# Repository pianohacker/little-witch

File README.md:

# Little WitCH

The Little WitCH is a tiny but capable dev board for the WCH32V307, boasting:

- The WCH32V307 itself, with a single RISC-V RV32IMACF core
- Gigabit Ethernet via the MXL86110C PHY
- Raspberry-Pi-compatible I/O (with caveats), exposing:
  - Two SPI buses
  - Two I2C buses
  - PCM audio out
  - SDIO/eMMC
  - and/or 28 3.3V GPIO pins
- USB-C 2.0
- USB-1.1 via Raspberry-Pi-Zero-compatible test points
- Tag-Connect TC2030 SWD debugging

## Raspberry Pi compatibility

The WCH32V307's pin remapping can't make it a perfect match for the Raspberry Pi's peripherals. The
biggest caveat is the SPI and PCM outputs, which are all multiplexed together and overlapping:

- SPI3 is exposed on the same pins as the Pi's SPI0 bus.
- PCM is exposed on the same pins as the Pi, but only supports output.
- SPI2 can be exposed on the same pins as the Pi's SPI1 bus, _but_ these pins overlap with the MDIO bus
  of the Ethernet PHY. Also, as these pins overlap with the PCM pins, SPI2 must be switched to by
  cutting and resoldering three solder jumpers below the USB-C port.

That said, this should still allow compatibility with a wide number of Pi Zero / Pi 4 HATs. Will
mention specific examples here as they are tested.

## Solder jumper reconfiguration

There are three sets of solder jumpers that can modify the behavior of this board:

- The jumpers mentioned above, which collectively switch pins 12, 35, and 40 between SPI2 and PCM
  (via I2S3). These default to PCM. **Note:** to be explicit, to switch to SPI2 on these pins, the
  bridge between the first two pads of all three jumpers must be cut and the 2nd and 3rd jumpers
  solder-bridged.
- A jumper to set the value of BOOT1. This defaults to 0.
- A jumper to enable the power LED, which defaults to lit.

## Authors

This is a collaboration between Jesse Weaver (pianohacker) and [Pikkolo Assembly](https://www.pikkoloassembly.com/).

## License

Little WitCH © 2026 by Jesse Weaver is licensed under CC BY-NC-SA 4.0. To view a copy of this license, visit https://creativecommons.org/licenses/by-nc-sa/4.0/

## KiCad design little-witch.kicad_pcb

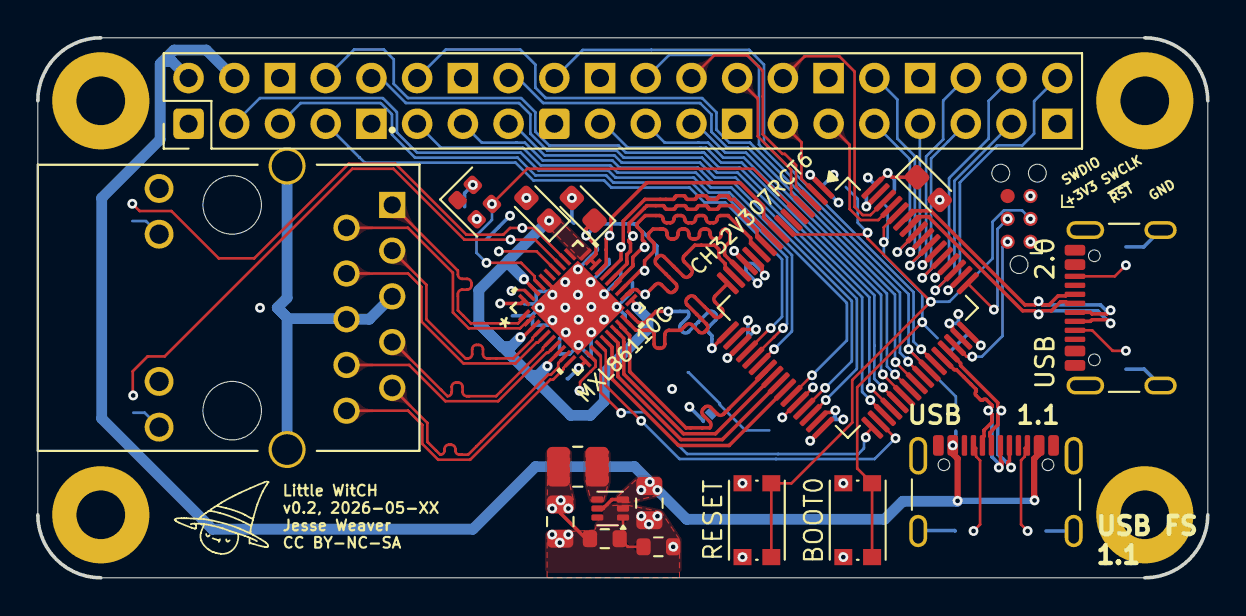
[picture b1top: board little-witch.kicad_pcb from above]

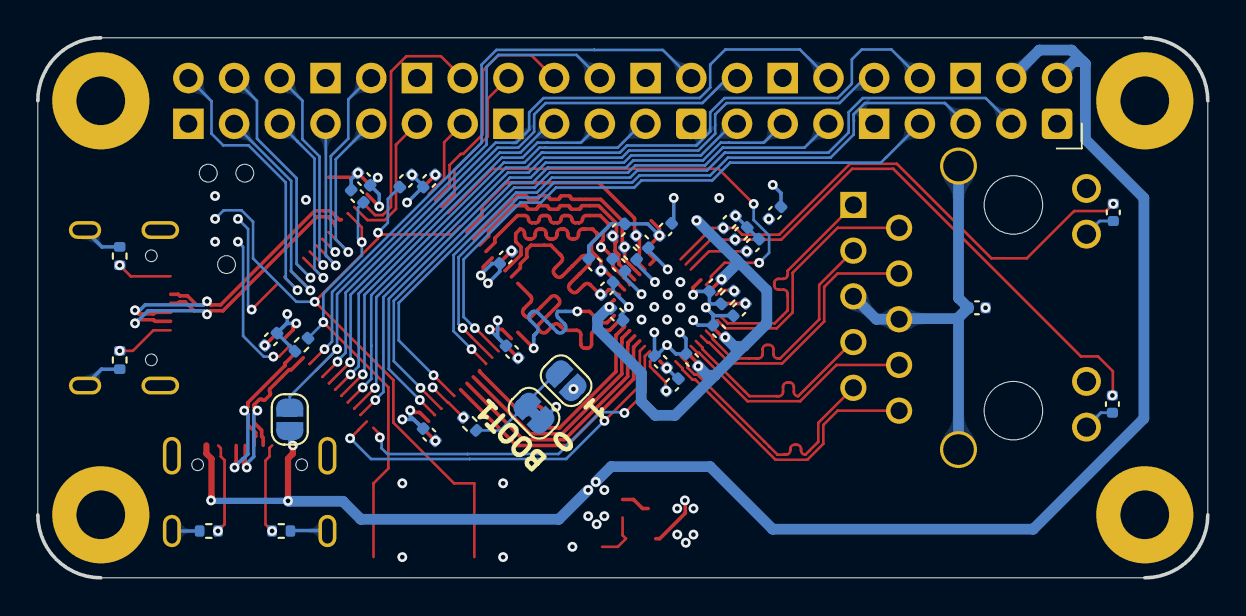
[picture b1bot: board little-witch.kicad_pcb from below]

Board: 4 copper layers, 65.0 x 30.0 mm, 62 parts (40 on the bottom side), 79 nets.

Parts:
C1, C7, C10: 10u; CP_EIA-2012-12_Kemet-R
C2, C3, C4, C5, C6, C8, C9, C11, C14, C18, C19, C20, C22, C23, C24, C26, C27: 100n; C_0402_1005Metric
C12: 4.7u; C_0805_2012Metric
C13: 22u; C_0805_2012Metric
H1, H2, H3, H4: MountingHole_Pad; MountingHole_2.7mm_M2.5_Pad
J1, J4: GCT-USB4105; USB_C_Receptacle_GCT_USB4105-xx-A_16P_TopMnt_Horizontal
J2: TMJG0803HENL; RJ45_TMJG0803HENL
J3: Conn_ARM_SWD_TagConnect_TC2030-NL; Tag-Connect_TC2030-IDC-NL_2x03_P1.27mm_Vertical
J5: Conn_02x20_Odd_Even; PinHeader_2x20_P2.54mm_Vertical
JP3, JP5: SolderJumper_2_Open; SolderJumper-2_P1.3mm_Open_RoundedPad1.0x1.5mm
JP4: SolderJumper_2_Open; SolderJumper-2_P1.3mm_Bridged_RoundedPad1.0x1.5mm
L1: 1u; L_1008_2520Metric
R3, R4, R8, R9: 5.1k; R_0402_1005Metric
R5, R17, R18, R19, R20, R21, R22: 1K; C_0402_1005Metric
R7, R10: 10k; R_0402_1005Metric
R11, R12: 100; C_0402_1005Metric
R13: 2.49K ±1%; R_0402_1005Metric
R14, R15, R16: 4.7K; C_0402_1005Metric
R23: 453K ±1%; R_0603_1608Metric
R24: 100K ±1%; R_0603_1608Metric
SW1: RESET; SW_Push_1P1T_NO_CK_KMR2
SW2: BOOT0; SW_Push_1P1T_NO_CK_KMR2
U1: CH32V307RCT6; LQFP-64_10x10mm_P0.5mm
U2: MXL86110C-AQB-R; QFN40_5X5_MXL
U3: TPS62A0568PDRLR; SOT-563
Y1: SIT8008BI-73-33N-25.000000; Oscillator_SMD_SiT_PQFN-4Pin_2.0x1.6mm

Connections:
+3V3: C1.1, C2.1, C3.1, C4.1, C5.1, C6.1, C9.1, C10.1, C11.1, C13.1, C14.1, C20.1, C22.1, C23.1, J2.11, J2.13, J3.1 (VCC), J5.1, J5.17, JP3.1 (A), L1.2, R5.2, R14.1, R15.1, R16.1, R21.1, R22.1, R23.2, SW2.1, U1.1 (VBAT), U1.13 (VDDA), U1.19 (VDD_4), U1.32 (VIO_1), U1.48 (VDD_2), U1.64 (VIO_3), U2.11 (VDDA3V3), U2.28 (VDDP), U2.29 (VDD3V3), U2.40 (VDDA3V3), Y1.4 (Vdd)
/ETH_CFG_LDO1: R16.2, U2.34 (GPHY_LED2/CFG_LDO1)
/ETH_SHIELD: C27.1, J2.5 (CT), J2.6 (CT__1), J2.SH (SHIELD)
/PA4: J5.7, U1.20 (DAC0/ADC4/PA4)
/PA5: J5.5, U1.21 (DAC1/ADC5/PA5)
/PA6: J5.3, U1.22 (ADC6/PA6)
/PA8: J5.12, U1.41 (PA8)
/PA9: J5.22, JP5.2 (B), U1.42 (PA9)
/PA10: J5.18, U1.43 (PA10)
/PA15: J5.40, U1.50 (PA15)
/PB1: J5.11, U1.27 (ADC9/PB1)
/PB2: R7.2, U1.28 (BOOT1/PB2)
/PB3: J5.33, U1.55 (PB3)
/PB4: J5.32, U1.56 (PB4)
/PB5: J5.31, U1.57 (PB5)
/PB8: J5.29, U1.61 (PB8)
/PB9: J5.28, U1.62 (PB9)
/PB10: J5.13, U1.29 (PB10)
/PB11: J5.15, U1.30 (PB11)
/PB14: J5.10, U1.35 (PB14)
/PB15: J5.8, U1.36 (PB15)
/PC6: J5.19, U1.37 (PC6/RXP)
/PC7: J5.21, U1.38 (PC7/RXN)
/PC8: J5.23, U1.39 (PC8/TXP)
/PC9: J5.16, U1.40 (PC9/TXN)
/PC10: J5.37, U1.51 (PC10)
/PC11: J5.38, U1.52 (PC11)
/PC12: J5.35, U1.53 (PC12)
/PC13: J5.27, U1.2 (PC13/TAMPER-RTC)
/PC14: J5.24, U1.3 (PC14/OSC32_IN)
/PC15: J5.26, U1.4 (PC15/OSC32_OUT)
/PD2: J5.36, U1.54 (PD2)
/TD1+: J2.1 (TD1+), U2.1 (TPIAP)
/TD1-: J2.2 (TD1-), U2.2 (TPIAN)
/TD2+: J2.3 (TD2+), U2.4 (TPIBP)
/TD2-: J2.4 (TD2-), U2.5 (TPIBN)
/TD3+: J2.7 (TD3+), U2.6 (TPICP)
/TD3-: J2.8 (TD3-), U2.7 (TPICN)
/TD4+: J2.9 (TD4+), U2.9 (TPIDP)
/TD4-: J2.10 (TD4-), U2.10 (TPIDN)
ETH_LED1: R11.2, R14.2, U2.32 (GPHY_LED0/CFG_EXT)
ETH_LED2: R12.2, R15.2, U2.33 (GPHY_LED1/CFG_LDO0)
ETH_MDC: U1.33 (PB12), U2.13 (MDC)
ETH_MDIO: U1.34 (PB13), U2.14 (MDIO)
ETH_RESET: R5.1, U2.12 (HRSTN)
ETH_RXC: R20.2, U1.8 (PC0/ADC10), U2.27 (RX_CLK/PHYAD1)
ETH_RXD0: R21.2, U1.10 (PC2/ADC12), U2.25 (RXD0/RXDLY)
ETH_RXD1: R19.2, U1.11 (PC3/ADC13), U2.24 (RXD1/TXDLY)
ETH_RXD2: R22.2, U1.14 (ADC0/WKUP/PA0), U2.23 (RXD2/PLLOFF)
ETH_RXD3: R17.2, U1.15 (ADC1/PA1), U2.22 (RXD3/PHYAD0)
ETH_RX_CTL: R18.2, U1.9 (PC1/ADC11), U2.26 (RX_CTL/PHYAD2)
ETH_TXC: U1.16 (ADC2/PA2), U2.19 (TX_CTL)
ETH_TXD0: U1.23 (ADC7/PA7), U2.18 (TXD0)
ETH_TXD1: U1.24 (PC4/ADC14), U2.17 (TXD1)
ETH_TXD2: U1.25 (PC5/ADC15), U2.16 (TXD2)
ETH_TXD3: U1.26 (ADC8/PB0), U2.15 (TXD3)
ETH_TX_CTL: U1.17 (ADC3/PA3), U2.20 (TX_CLK)
GND: C1.2, C2.2, C3.2, C4.2, C5.2, C6.2, C7.2, C8.1, C9.2, C10.2, C11.2, C12.2, C13.2, C18.2, C19.2, C20.2, C22.2, C23.2, C24.2, C26.2, C27.2, H1.1 (1_1), H2.1 (1_1), H3.1 (1_1), H4.1 (1_1), J1.A1 (GND), J1.A12 (GND), J1.B1 (GND), J1.B12 (GND), J1.SH (SHIELD), J3.5 (GND), J4.A1 (GND), J4.A12 (GND), J4.B1 (GND), J4.B12 (GND), J4.SH (SHIELD), J5.6, J5.9, J5.14, J5.20, J5.25, J5.30, J5.34, J5.39, JP4.1 (A), R3.2, R4.1, R8.2, R9.1, R10.1, R13.2, R17.1, R18.1, R19.1, R20.1, R24.1, SW1.1, U1.12 (VSSA), U1.18 (VSS_4), U1.31 (VSS_1), U1.47 (VSS_2), U1.63 (VSS_3), U2.36 (XTAL1), U2.41 (GND), U3.2 (GND), Y1.2 (GND)
NRST: C8.2, J3.3 (~RESET), SW1.2, U1.7 (NRST)
unnamed: J1.A5 (CC1), R3.1
unnamed: J1.B5 (CC2), R4.2
unnamed: J2.12, R11.1
unnamed: J2.14, R12.1
unnamed: J4.A5 (CC1), R8.1
unnamed: J4.B5 (CC2), R9.2
unnamed: JP3.2 (B), JP4.2 (B), R7.1
unnamed: C14.2, R10.2, SW2.2, U1.60 (BOOT0)
unnamed: R13.1, U2.39 (RCAL)
unnamed: R23.1, R24.2, U3.1 (FB)
unnamed: L1.1, U3.4 (SW)
SWCLK: J3.4 (SWCLK), U1.49 (SWCLK/PA14)
SWDIO: J3.2 (SWDIO), U1.46 (SWDIO/PA13)
SYS_CLK: U1.5 (OSC_IN/PD0), U2.37 (XTAL2/CLK), Y1.3 (OUT)
USB1_DN: J1.A7 (D-), J1.B7 (D-), U1.44 (USB1_DM/PA11)
USB1_DP: J1.A6 (D+), J1.B6 (D+), U1.45 (USB1_DP/PA12)
USB1_VBUS: C12.1, J1.A4 (VBUS), J1.A9 (VBUS), J1.B4 (VBUS), J1.B9 (VBUS), J5.2, J5.4, JP5.1 (A), U3.3 (VIN), U3.5 (EN)
USB2_DN: J4.A7 (D-), J4.B7 (D-), U1.58 (USB2_DM/PB6)
USB2_DP: J4.A6 (D+), J4.B6 (D+), U1.59 (USB2_DP/PB7)
VDD_ETH: C7.1, C18.1, C19.1, C24.1, C26.1, U2.3 (VDDA1V1), U2.8 (VDDA1V1), U2.21 (VDD), U2.30 (DCDC_REGO), U2.38 (VDDA1V1)

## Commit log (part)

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2026-04-17 Add 3d model to kycon footprint
2026-04-24 v0.1 without Ethernet or voltage reg
2026-04-28 Import all symbols into project library
2026-04-28 Remove core symbols from project library
2026-04-28 Add README.md
2026-04-29 Start of ethernet
2026-04-30 Ethernet schematic done
2026-04-30 Base ethernet signals routed
2026-04-30 First ethernet jack routed
2026-05-01 Etherent MDI rerouted with correct trace widths
2026-05-01 MDI RX/TX length matched
2026-05-01 USB routing
2026-05-01 MCU decoupling
2026-05-01 Start on PHY decoupling
2026-05-01 More PHY passives
2026-05-02 PHY RX routing and power
2026-05-02 Ethernet shielding
2026-05-03 Some GPIO and power routing
2026-05-03 Continued GPIO
2026-05-04 Shrink vias to 0.55mm
2026-05-06 GPIO routing
2026-05-06 More GPIO routing
2026-05-07 Yet more GPIO routing
2026-05-07 GPIO fully routed
2026-05-07 Ethernet LEDs and start of power
2026-05-07 Routing tweaks
2026-05-08 Start of better GPIO routing
2026-05-08 Better GPIO routing
2026-05-08 Power regulation
2026-05-08 Debug routing
2026-05-08 Reset and BOOT0 buttons
2026-05-08 Missing power schematic
2026-05-08 USB VBUS diode
2026-05-09 Silkscreen tweaks
2026-05-09 Final silkscreen, v0.2
2026-05-09 Pikkolo QR code
